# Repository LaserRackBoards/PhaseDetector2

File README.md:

# PhaseDetector2
Phase detector with wide bandwidth, for PDH lock

* SYPD-1, SYPD-2, SYPD-52W phase detector
* [ADC-10-1R](https://www.minicircuits.com/pdfs/ADC-10-1R) directional coupler, 10.5dB coupling, 0.7dB mainline loss
* [BUF602](https://www.ti.com/product/BUF602) buffer amp
* [ADA4898-1](https://www.analog.com/en/products/ada4898-1.html) low noise op-amp
* [LT1568](https://www.analog.com/en/products/lt1568.html) low noise active filter

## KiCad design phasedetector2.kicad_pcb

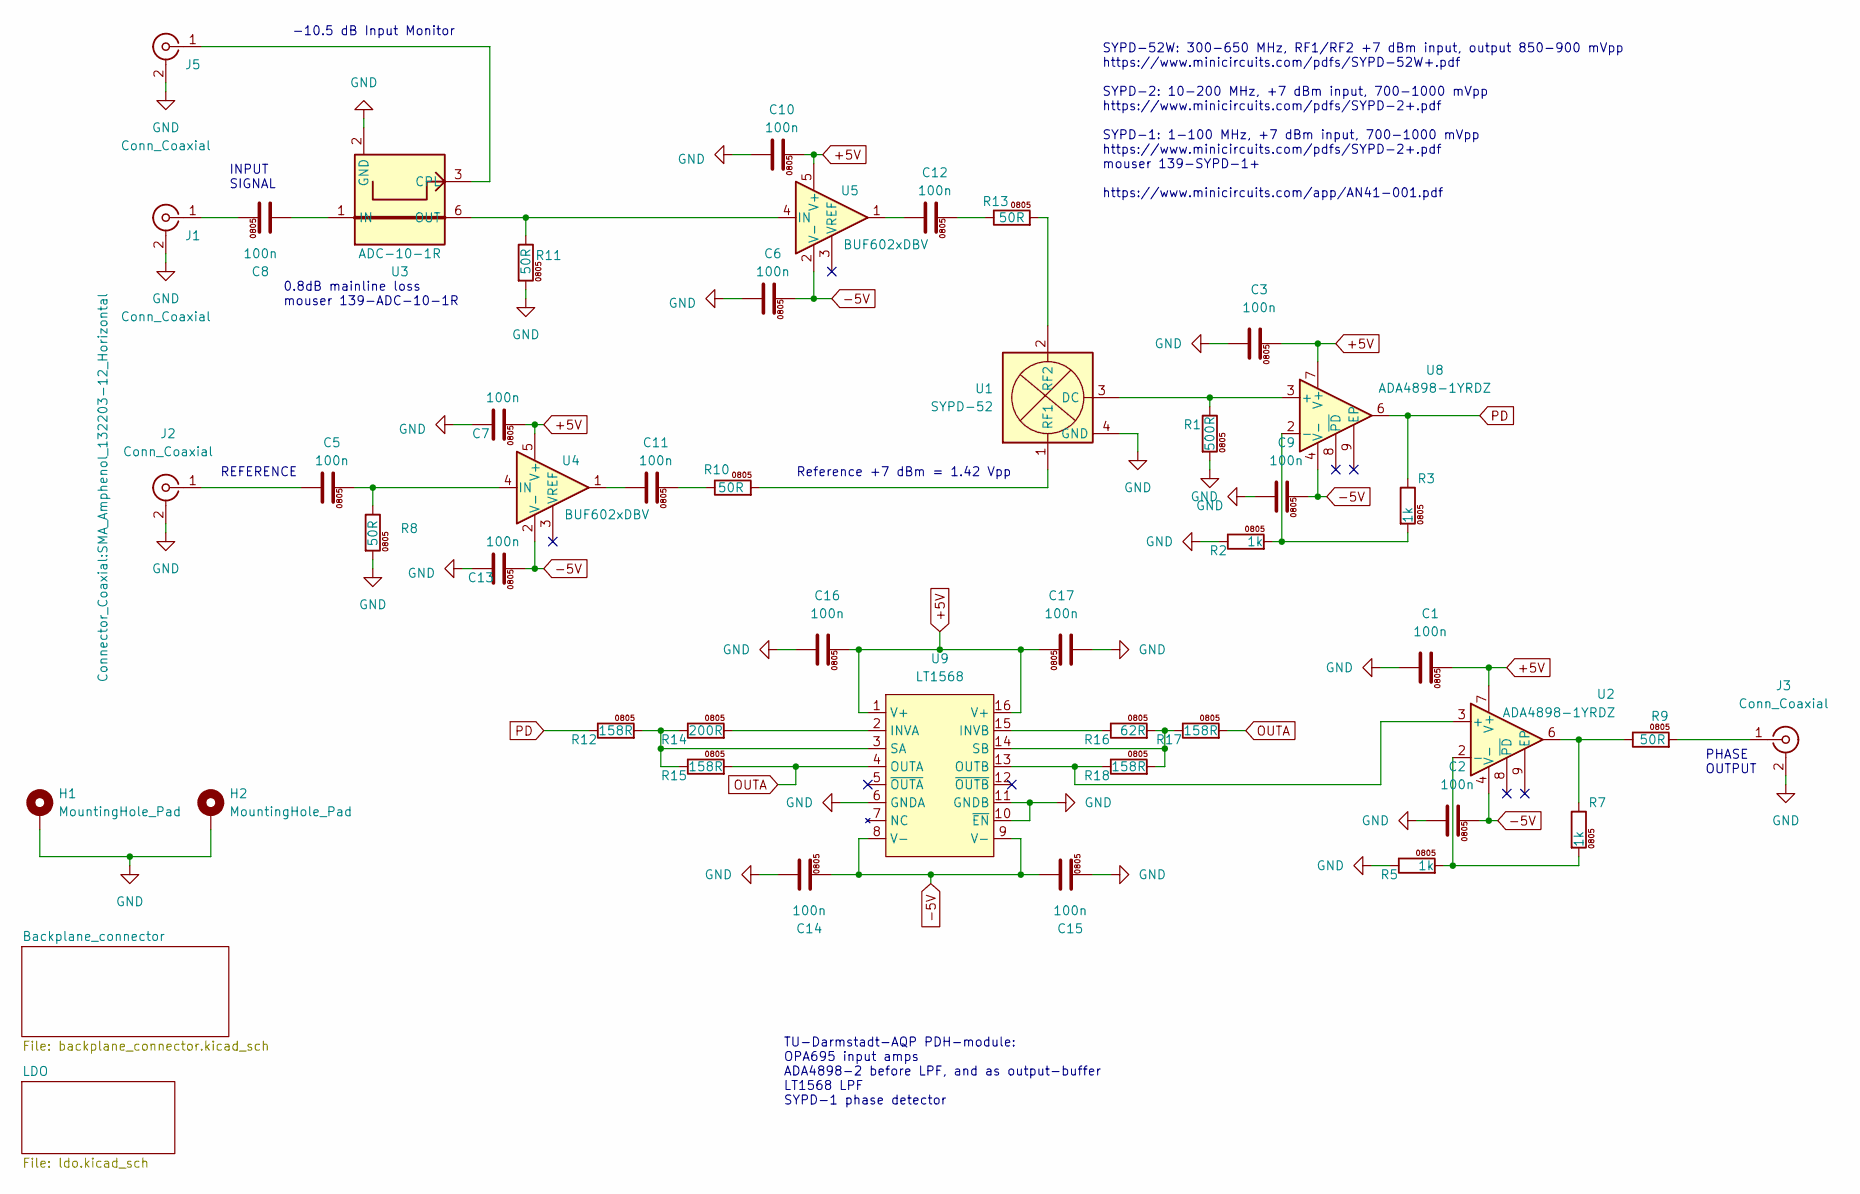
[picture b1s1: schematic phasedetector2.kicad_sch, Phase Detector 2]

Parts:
C1, C2, C3, C5, C6, C7, C8, C9, C10, C11, C12, C13, C14, C15, C16, C17: 100n; C_0805_2012Metric
H1, H2: MountingHole_Pad; MountingHole_2.7mm_M2.5_DIN965_Pad
J1, J2, J3, J5: Conn_Coaxial; SMA_Amphenol_132203-12_Horizontal
R1: 500R; R_0805_2012Metric
R2, R3, R5, R7: 1k; R_0805_2012Metric
R8, R9, R10, R11, R13: 50R; R_0805_2012Metric
R12, R15, R17, R18: 158R; R_0805_2012Metric
R14: 200R; R_0805_2012Metric
R16: 62R; R_0805_2012Metric
U1: SYPD-52; Mini-Circuits_TTT167_LandPatternPL-079
U2, U8: ADA4898-1YRDZ; SOIC-8-1EP_3.9x4.9mm_P1.27mm_EP2.29x3mm
U3: ADC-10-1R; Mini-Circuits_CD542_LandPatternPL-094
U4, U5: BUF602xDBV; SOT-23-5
U9: LT1568; SSOP-16_3.9x4.9mm_P0.635mm

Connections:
+5V: C1.2, C3.2, C7.2, C10.2, C16.2, C17.2, U2.7 (V+), U4.5 (V+), U5.5 (V+), U8.7 (V+), U9.1 (V+), U9.16 (V+); also elsewhere on the board
-5V: C2.2, C6.2, C9.2, C13.2, C14.2, C15.1, U2.4 (V-), U4.2 (V-), U5.2 (V-), U8.4 (V-), U9.8 (V-), U9.9 (V-); also elsewhere on the board
GND: C1.1, C2.1, C3.1, C6.1, C7.1, C9.1, C10.1, C13.1, C14.1, C15.2, C16.1, C17.1, H1.1, H2.1, J1.2 (Ext), J2.2 (Ext), J3.2 (Ext), J5.2 (Ext), R1.2, R2.1, R5.1, R8.2, R11.2, U1.4 (GND), U1.5 (GND), U1.6 (GND), U3.2 (GND), U3.5 (GND), U9.6 (GNDA), U9.10 (~EN), U9.11 (GNDB); also elsewhere on the board
unnamed: C11.1, U4.1
unnamed: C11.2, R10.1
unnamed: C12.1, U5.1
unnamed: C12.2, R13.1
unnamed: C8.2, J1.1 (In)
unnamed: C5.1, J2.1 (In)
unnamed: J3.1 (In), R9.2
unnamed: J5.1 (In), U3.3 (CPL)
unnamed: R7.1, R9.1, U2.6
unnamed: R1.1, U1.3 (DC), U8.3 (+)
unnamed: R10.2, U1.1 (RF1)
unnamed: R13.2, U1.2 (RF2)
unnamed: R18.1, U2.3 (+), U9.13 (OUTB)
unnamed: R5.2, R7.2, U2.2 (-)
unnamed: C8.1, U3.1 (IN)
unnamed: R11.1, U3.6 (OUT), U5.4 (IN)
unnamed: C5.2, R8.1, U4.4 (IN)
unnamed: R2.2, R3.2, U8.2 (-)
unnamed: R14.2, U9.2 (INVA)
unnamed: R16.1, U9.15 (INVB)
unnamed: R12.2, R14.1, R15.1, U9.3 (SA)
unnamed: R16.2, R17.1, R18.2, U9.14 (SB)
OUTA: R15.2, R17.2, U9.4 (OUTA)
PD: R3.1, R12.1, U8.6

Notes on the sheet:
PHASE OUTPUT
0.8dB mainline loss mouser 139-ADC-10-1R
Reference +7 dBm = 1.42 Vpp
SYPD-52W: 300-650 MHz, RF1/RF2 +7 dBm input, output 850-900 mVpp https://www.minicircuits.com/pdfs/SYPD-52W+.pdf SYPD-2: 10-200 MHz, +7 dBm input, 700-1000 mVpp https://www.minicircuits.com/pdfs/SYPD-2+.pdf SYPD-1: 1-100 MHz, +7 dBm input, 700-1000 mVpp https://www.minicircuits.com/pdfs/SYPD-2+.pdf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
INPUT SIGNAL
REFERENCE
TU-Darmstadt-AQP PDH-module: OPA695 input amps ADA4898-2 before LPF, and as output-buffer LT1568 LPF SYPD-1 phase detector
-10.5 dB Input Monitor

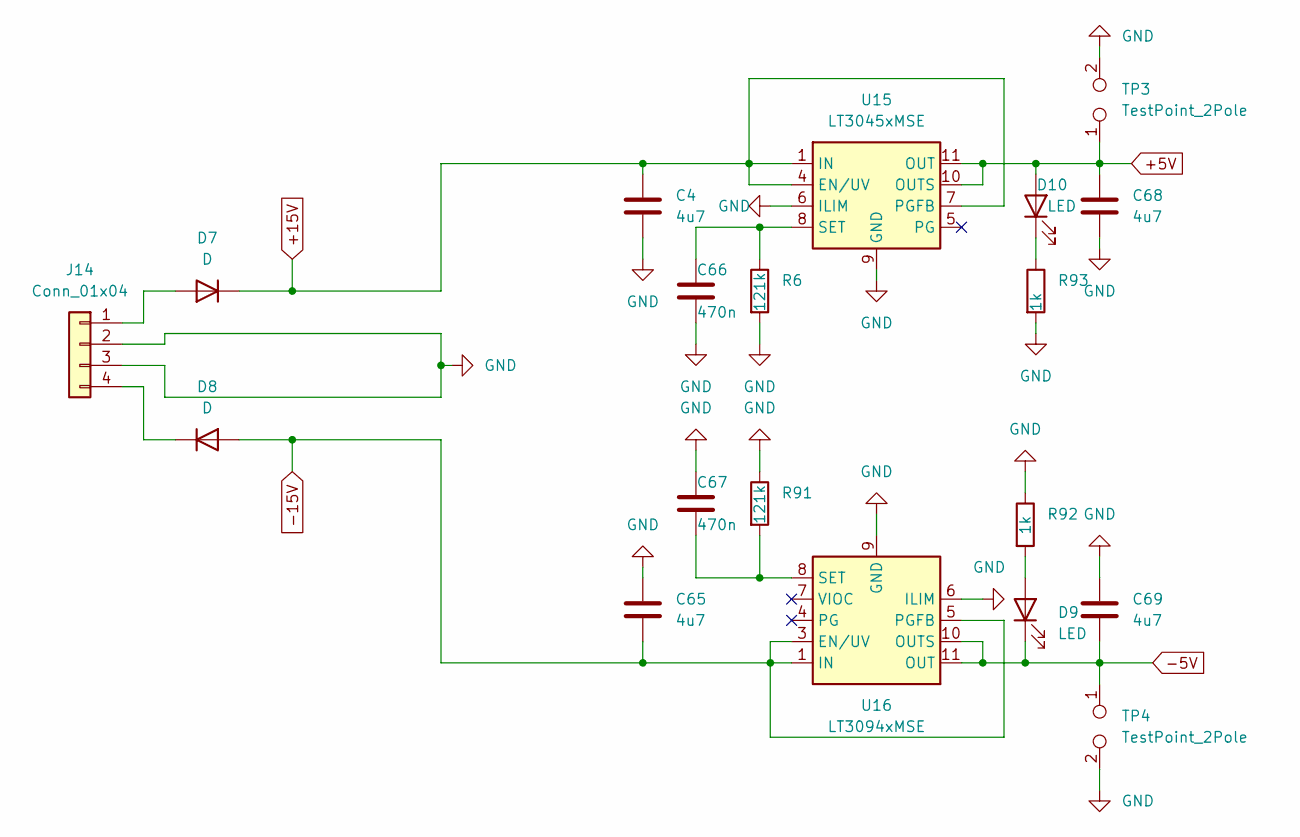
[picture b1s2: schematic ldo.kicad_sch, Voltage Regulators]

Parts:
C4, C65, C68, C69: 4u7; C_0805_2012Metric
C66, C67: 470n; C_0805_2012Metric
D7, D8: D; D_SMB
D9, D10: LED; LED_0805_2012Metric
J14: Conn_01x04; TerminalBlock_TE_282834-4_1x04_P2.54mm_Horizontal
R6, R91: 121k; R_0805_2012Metric
R92, R93: 1k; R_0805_2012Metric
TP3, TP4: TestPoint_2Pole; TestPoint_2Pads_Pitch2.54mm_Drill0.8mm
U15: LT3045xMSE; MSOP-12-1EP_3x4mm_P0.65mm_EP1.65x2.85mm
U16: LT3094xMSE; MSOP-12-1EP_3x4mm_P0.65mm_EP1.65x2.85mm

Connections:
+5V: C68.1, D10.2 (A), TP3.1, U15.10 (OUTS), U15.11 (OUT), U15.12 (OUT); also elsewhere on the board
+15V: C4.1, D7.1 (K), U15.1 (IN), U15.2 (IN), U15.3 (IN), U15.4 (EN/UV), U15.7 (PGFB); also elsewhere on the board
-5V: C69.2, D9.1 (K), TP4.1, U16.10 (OUTS), U16.11 (OUT), U16.12 (OUT); also elsewhere on the board
-15V: C65.2, D8.2 (A), U16.1 (IN), U16.2 (IN), U16.3 (EN/UV), U16.5 (PGFB), U16.13 (IN); also elsewhere on the board
GND: C4.2, C65.1, C66.2, C67.1, C68.2, C69.1, J14.2, J14.3, R6.2, R91.1, R92.1, R93.2, TP3.2, TP4.2, U15.6 (ILIM), U15.9 (GND), U15.13 (GND), U16.6 (ILIM), U16.9 (GND); also elsewhere on the board
unnamed: D7.2 (A), J14.1
unnamed: D8.1 (K), J14.4
unnamed: D9.2 (A), R92.2
unnamed: D10.1 (K), R93.1
unnamed: C66.1, R6.1, U15.8 (SET)
unnamed: C67.2, R91.2, U16.8 (SET)

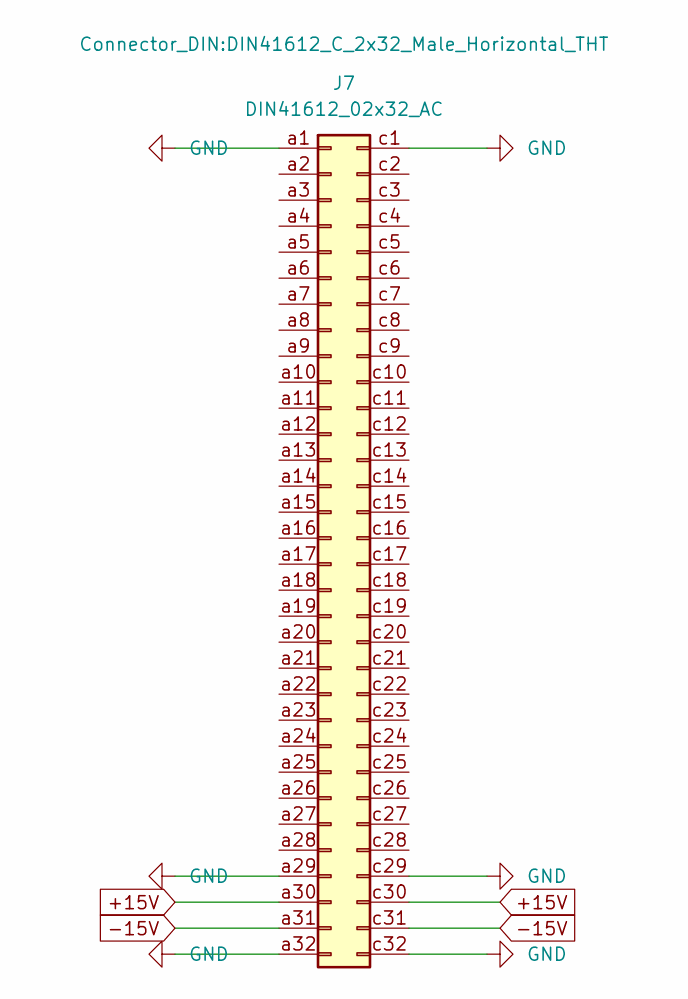
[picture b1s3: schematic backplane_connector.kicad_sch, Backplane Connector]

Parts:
J7: DIN41612_02x32_AC; DIN41612_C_2x32_Male_Horizontal_THT

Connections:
+15V: J7.a30, J7.c30; also elsewhere on the board
-15V: J7.a31, J7.c31; also elsewhere on the board
GND: J7.a1, J7.a29, J7.a32, J7.c1, J7.c29, J7.c32; also elsewhere on the board

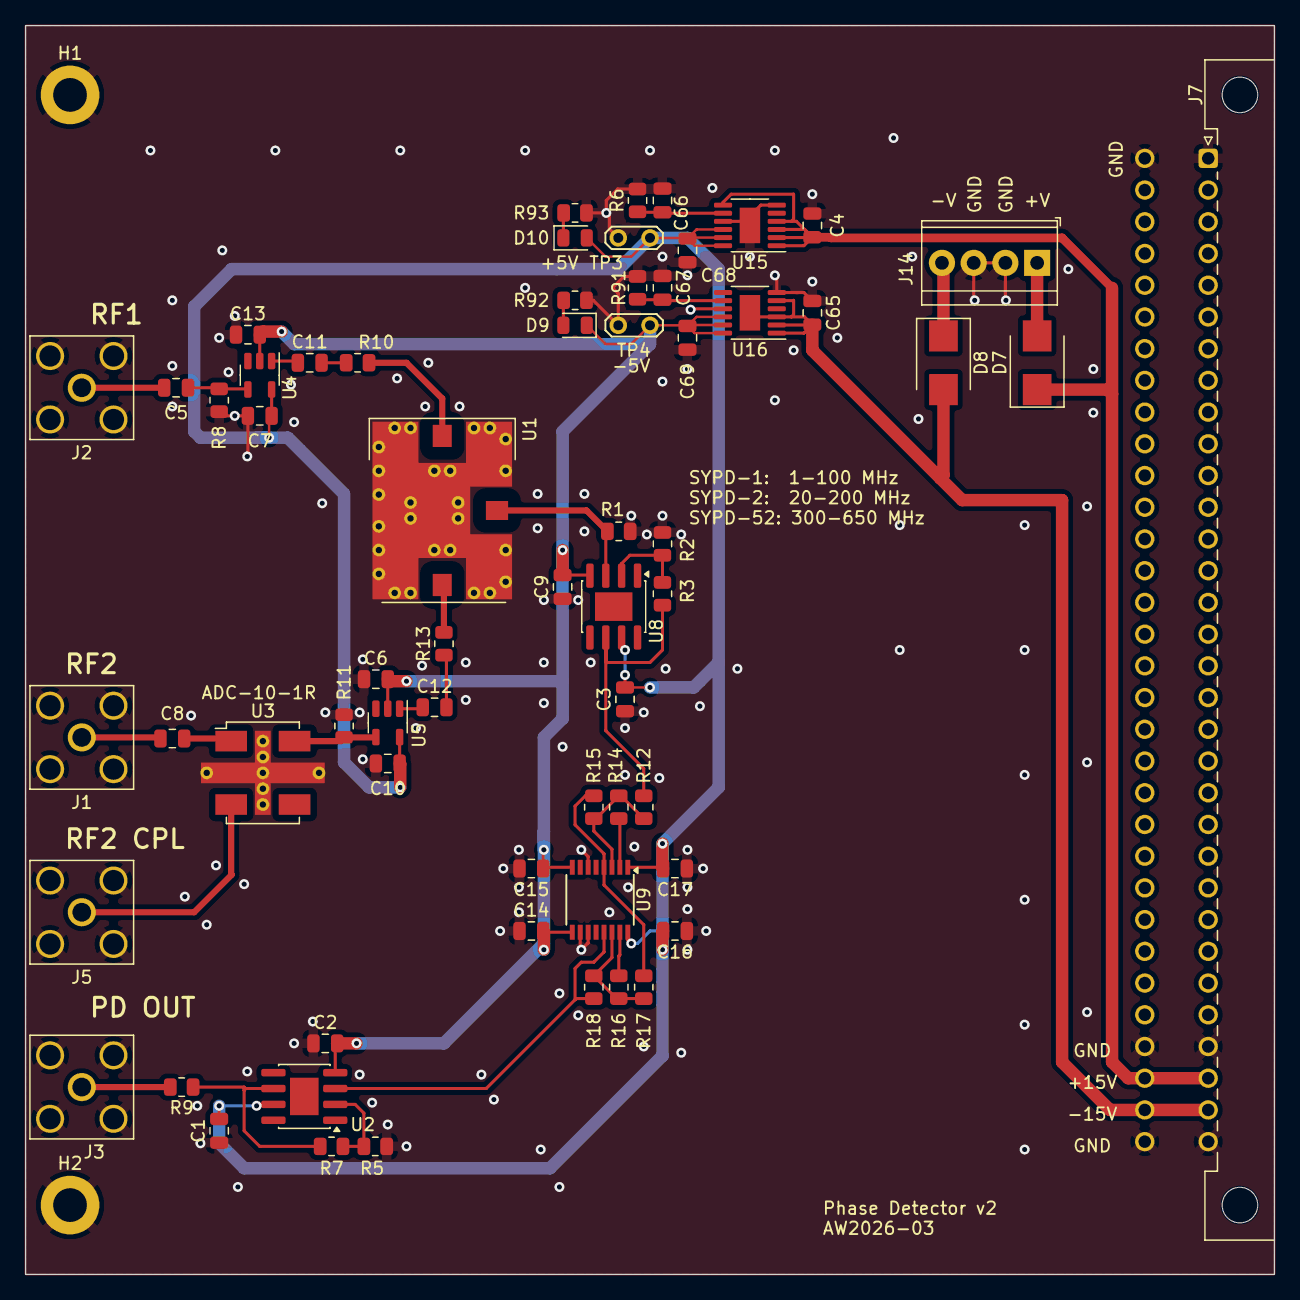
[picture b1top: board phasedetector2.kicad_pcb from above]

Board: 2 copper layers, 100.0 x 100.0 mm, 65 parts (0 on the bottom side), 35 nets.

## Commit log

2026-03-26 layout
2026-04-04 kicad 10
